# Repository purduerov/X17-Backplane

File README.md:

# Readme for X17-Backplane
This board routes signals and power between all the boards

Whenever you make a new part, download the datasheet and save it here _**and**_ with the part in the parts library

Always pull other people's changes before beginning to work
`git pull`

Be sure to push your changes after  working on them. Run:
1. `git add .` to add any files in this directory or a subdirectory
or `git add -u` to add any modified files
2. (Optional) `git clean -nX` to see what ignored files can be removed
	`git clean -fX` removes ignored files (Eagle backups)
3. `git commit -m "helpful commit message"` with a description of the work that you did
4. `git push` to push your work to github

Other helpful commands
* `git status` says information about modified and staged files
* `git log` shows the recent commits of the repository
* `git log filename.extension` show the recent commits for just that file
* `git checkout first-couple-letter-of-commit-id` lets you go back to a previous version
* `git checkout master` brings you back to the latest commit
* `git tag` lists the tags
* `git tag -a orderX -m "the version of the board placed for the X'th order"` tag a specific commit
* `git push --tags` needed to push tags to remote
* `git show orderX` show the commit log for the given tag
* `git checkout orderX` go back and interact with the files at the tagged commit

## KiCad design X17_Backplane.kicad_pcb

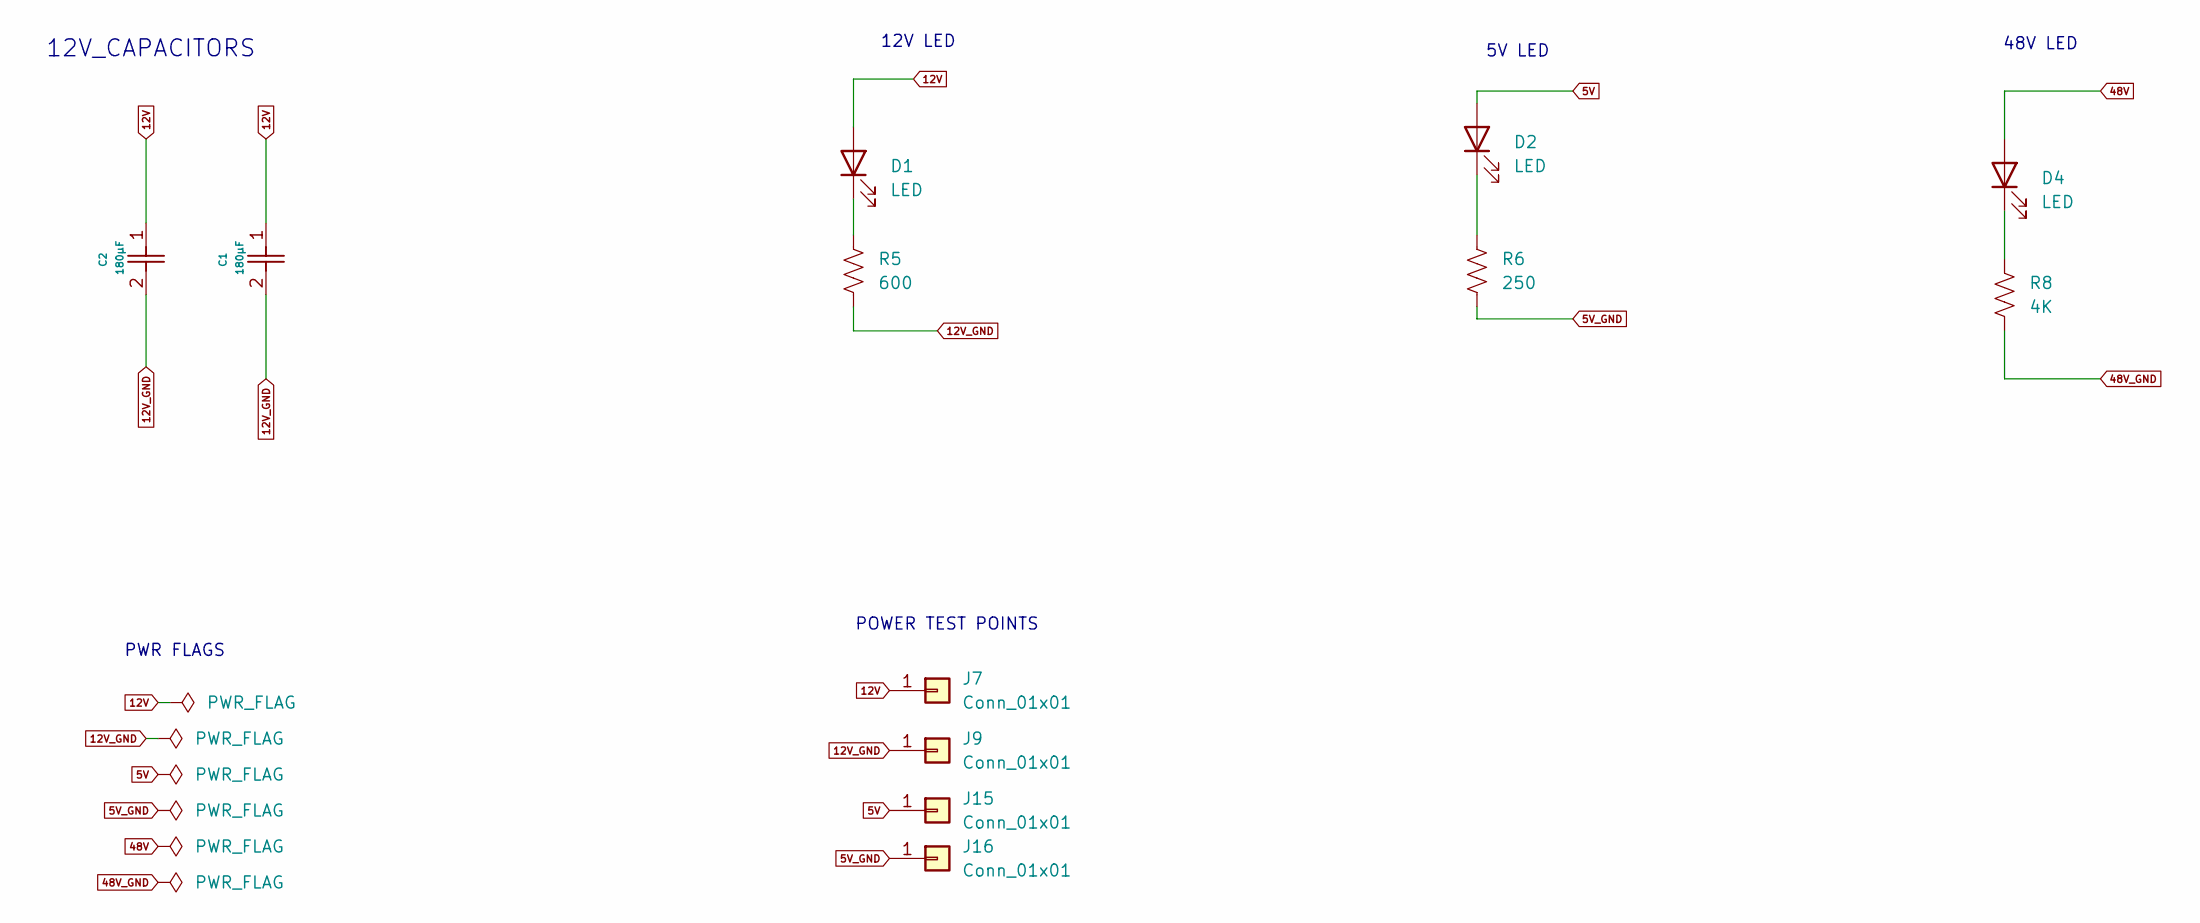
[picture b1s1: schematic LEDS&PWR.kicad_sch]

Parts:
C1, C2: 180μF; CAP_FT_F_PAN
D1, D2, D4: LED; LED_0805_2012Metric_Pad1.15x1.40mm_HandSolder
J7, J9, J15, J16: Conn_01x01; TestPoint_Pad_D4.0mm
R5: 600; R_0603_1608Metric_Pad0.98x0.95mm_HandSolder
R6: 250; R_0603_1608Metric_Pad0.98x0.95mm_HandSolder
R8: 4K; R_0603_1608Metric_Pad0.98x0.95mm_HandSolder

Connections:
5V: D2.2 (A), J15.1; also elsewhere on the board
5V_GND: J16.1, R6.2; also elsewhere on the board
12V: C1.1, C2.1, D1.2 (A), J7.1; also elsewhere on the board
12V_GND: C1.2, C2.2, J9.1, R5.2; also elsewhere on the board
48V: D4.2 (A); also elsewhere on the board
48V_GND: R8.2; also elsewhere on the board
unnamed: D1.1 (K), R5.1
unnamed: D2.1 (K), R6.1
unnamed: D4.1 (K), R8.1

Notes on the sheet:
12V_CAPACITORS
POWER TEST POINTS
12V LED
5V LED
48V LED
PWR FLAGS

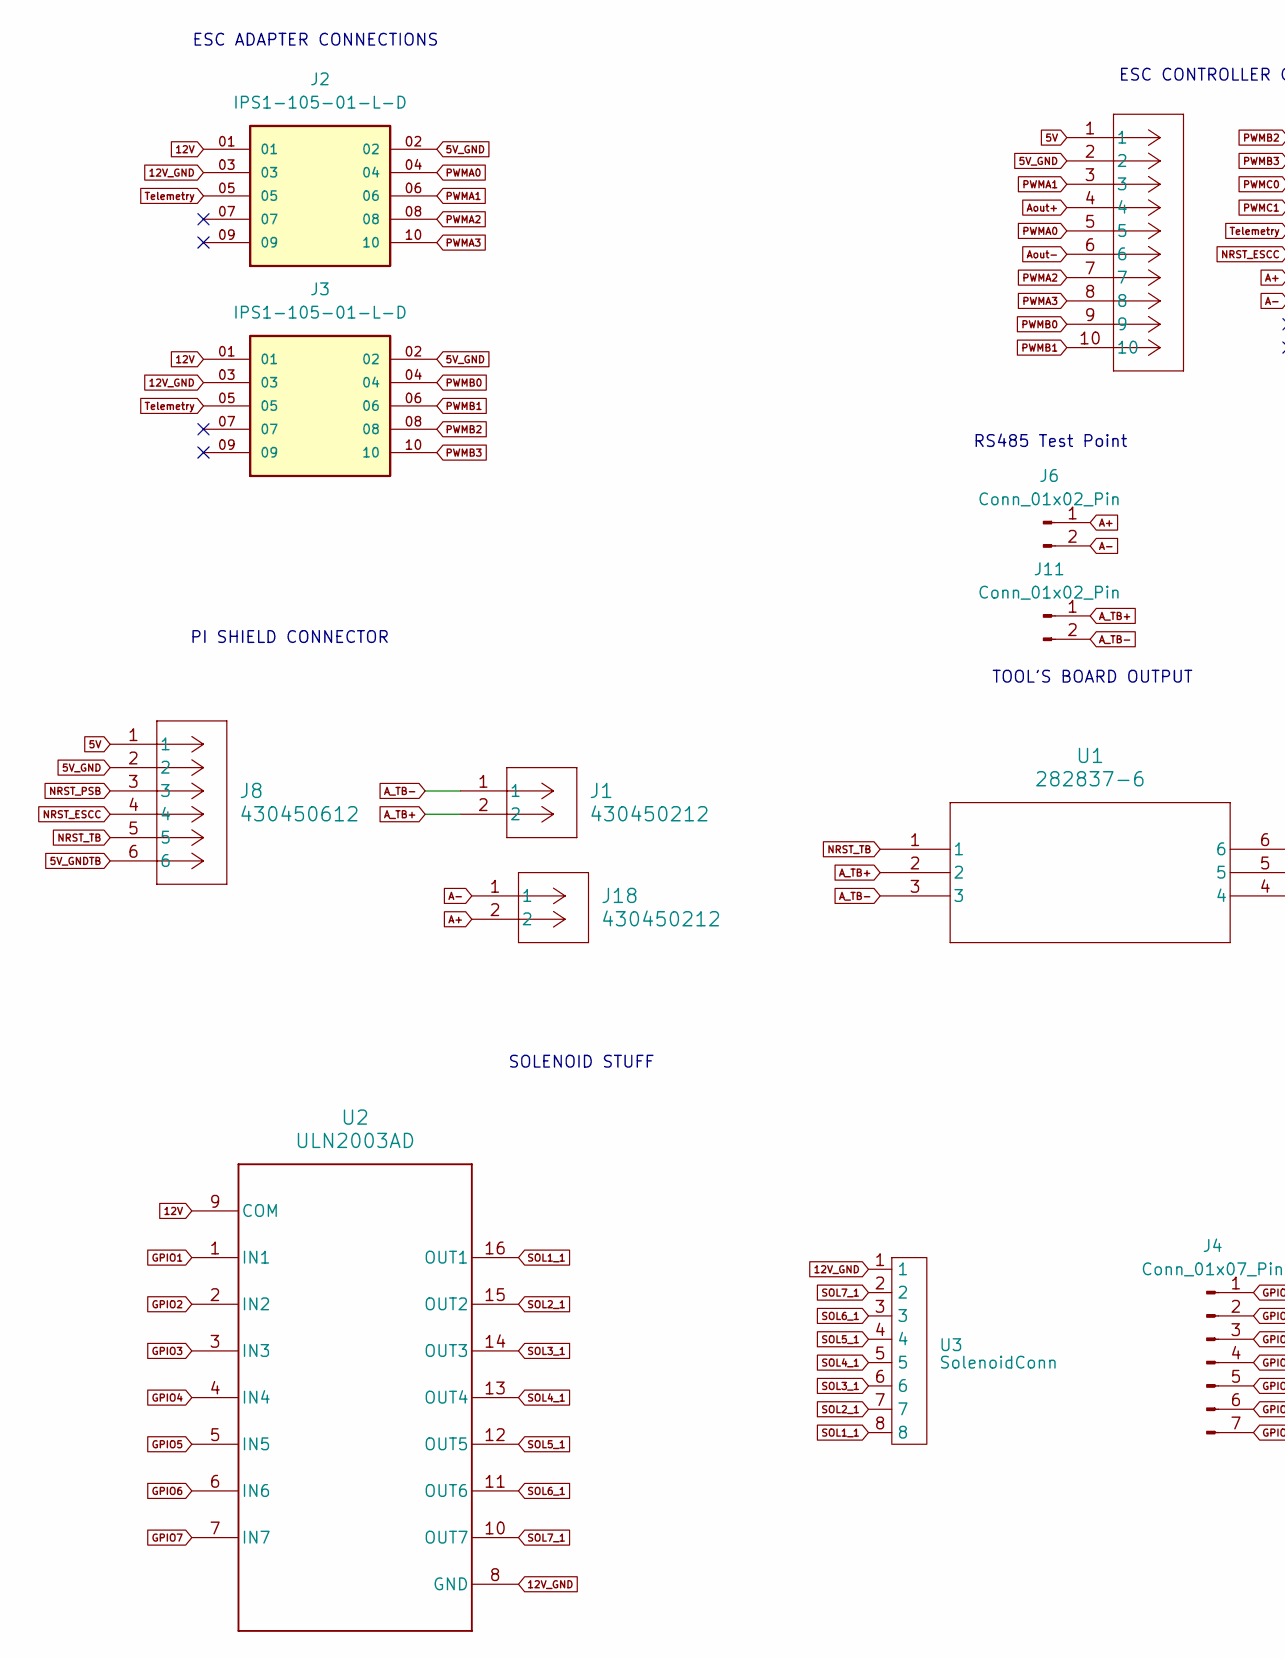
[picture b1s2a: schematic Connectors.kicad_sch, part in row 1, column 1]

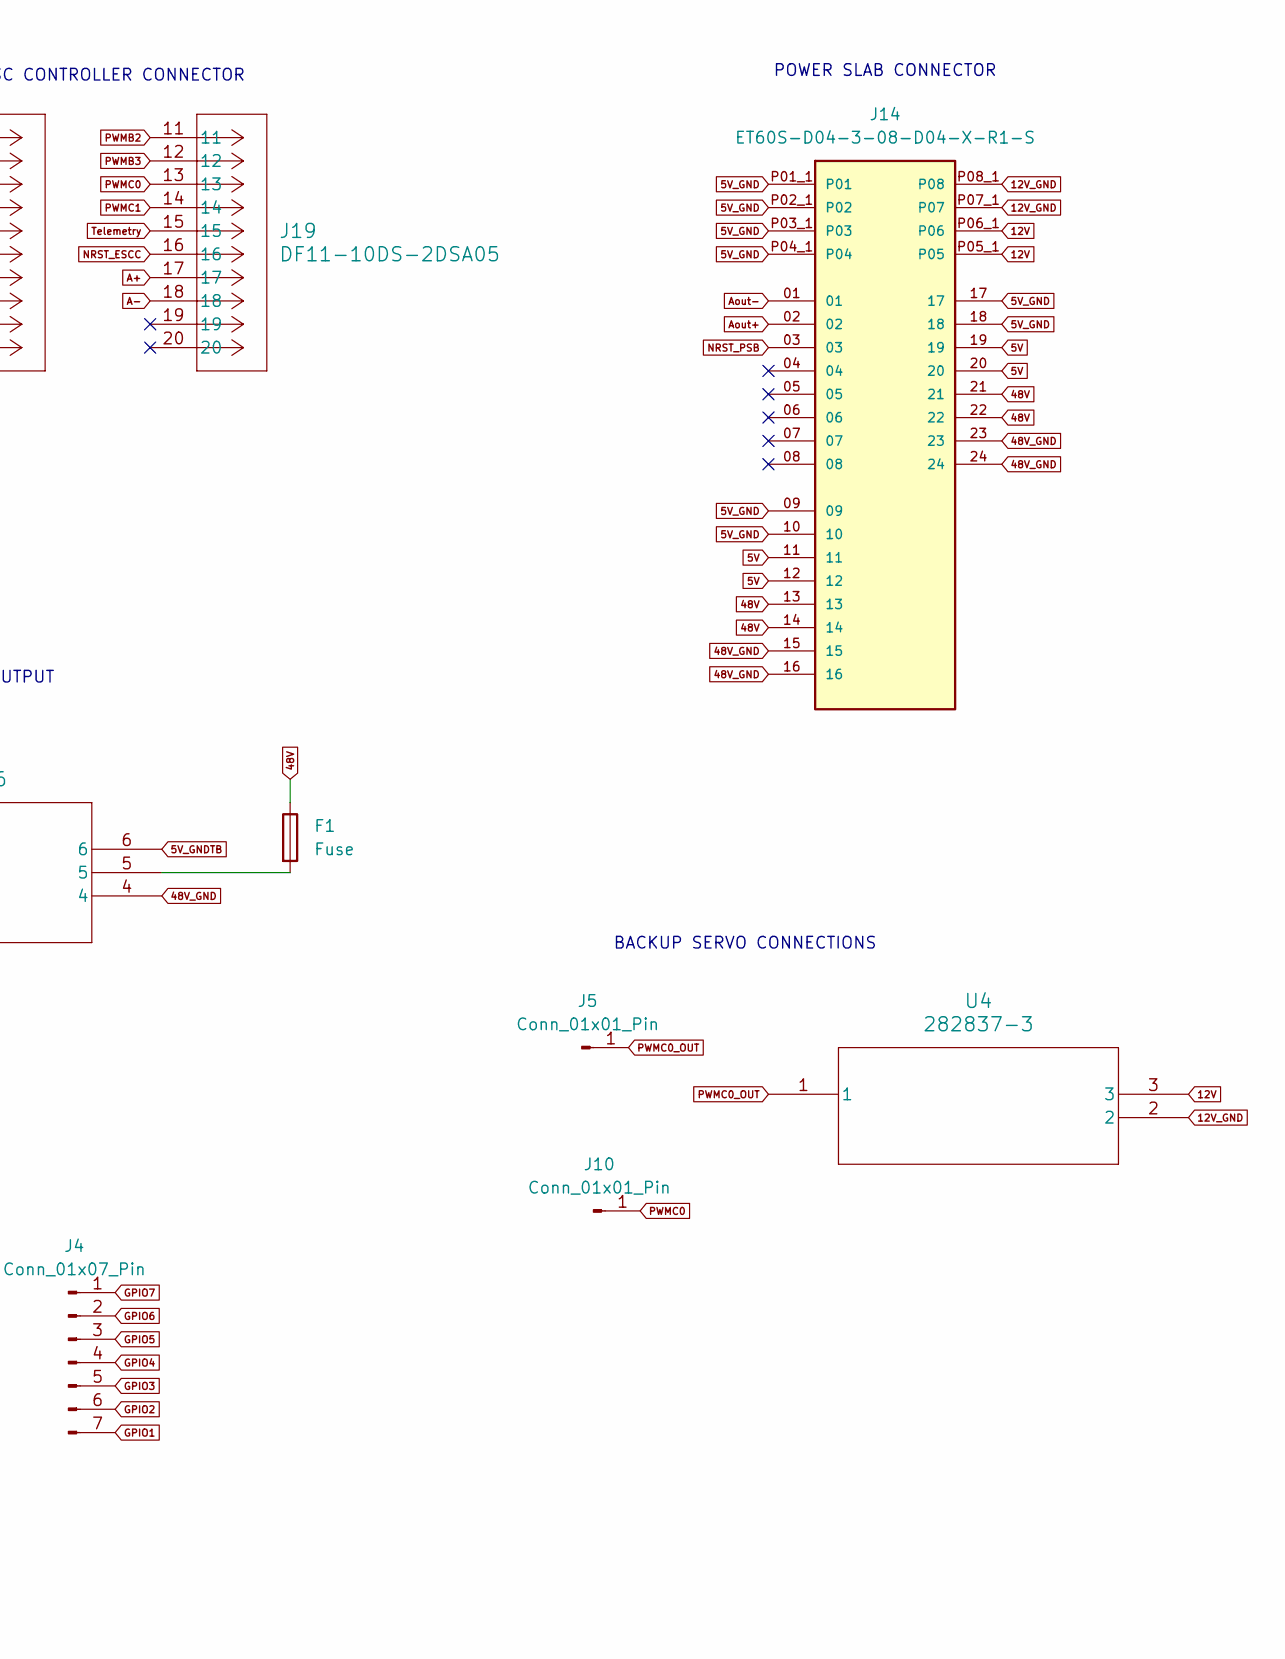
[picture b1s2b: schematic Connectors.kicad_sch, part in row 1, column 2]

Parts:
F1: Fuse; Fuse_Littelfuse-NANO2-451_453
J1, J18: 430450212; CON_430450212_MOL
J2, J3: IPS1-105-01-L-D; PWM, 12V, GND JST Connector (real); PARTREV R
J4: Conn_01x07_Pin; PinHeader_1x07_P2.54mm_Vertical
J5, J10: Conn_01x01_Pin; PinHeader_1x01_P2.54mm_Vertical
J6, J11: Conn_01x02_Pin; PinHeader_1x02_P2.54mm_Vertical
J8: 430450612; CON_430450612_MOL
J14: ET60S-D04-3-08-D04-X-R1-S; SAMTEC_ET60S-D04-3-08-D04-X-R1-S; PARTREV G
J19: DF11-10DS-2DSA05; CON10_2X5_UF_DF11_HIR
U1: 282837-6; 282837-6_TYC
U2: ULN2003AD; D0016A_L
U3: SolenoidConn; PHOENIX_1778612
U4: 282837-3; 282837-3_TYC

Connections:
5V: J8.1, J14.11, J14.12, J14.19, J14.20, J19.1; also elsewhere on the board
5V_GND: J2.02, J3.02, J8.2, J14.09, J14.10, J14.17, J14.18, J14.P01_1 (P01), J14.P02_1 (P02), J14.P03_1 (P03), J14.P04_1 (P04), J19.2; also elsewhere on the board
5V_GNDTB: J8.6, U1.6
12V: J2.01, J3.01, J14.P05_1 (P05), J14.P06_1 (P06), U2.9 (COM), U4.3; also elsewhere on the board
12V_GND: J2.03, J3.03, J14.P07_1 (P07), J14.P08_1 (P08), U2.8 (GND), U3.1, U4.2; also elsewhere on the board
48V: F1.1, J14.13, J14.14, J14.21, J14.22; also elsewhere on the board
48V_GND: J14.15, J14.16, J14.23, J14.24, U1.4; also elsewhere on the board
A+: J6.1, J18.2, J19.17
A-: J6.2, J18.1, J19.18
A_TB+: J1.2, J11.1, U1.2
A_TB-: J1.1, J11.2, U1.3
Aout+: J14.02, J19.4
Aout-: J14.01, J19.6
GPIO1: J4.7, U2.1 (IN1)
GPIO2: J4.6, U2.2 (IN2)
GPIO3: J4.5, U2.3 (IN3)
GPIO4: J4.4, U2.4 (IN4)
GPIO5: J4.3, U2.5 (IN5)
GPIO6: J4.2, U2.6 (IN6)
GPIO7: J4.1, U2.7 (IN7)
NRST_ESCC: J8.4, J19.16
NRST_PSB: J8.3, J14.03
NRST_TB: J8.5, U1.1
unnamed: F1.2, U1.5
PWMA0: J2.04, J19.5
PWMA1: J2.06, J19.3
PWMA2: J2.08, J19.7
PWMA3: J2.10, J19.8
PWMB0: J3.04, J19.9
PWMB1: J3.06, J19.10
PWMB2: J3.08, J19.11
PWMB3: J3.10, J19.12
PWMC0: J10.1, J19.13
PWMC0_OUT: J5.1, U4.1
PWMC1: J19.14
SOL1_1: U2.16 (OUT1), U3.8
SOL2_1: U2.15 (OUT2), U3.7
SOL3_1: U2.14 (OUT3), U3.6
SOL4_1: U2.13 (OUT4), U3.5
SOL5_1: U2.12 (OUT5), U3.4
SOL6_1: U2.11 (OUT6), U3.3
SOL7_1: U2.10 (OUT7), U3.2
Telemetry: J2.05, J3.05, J19.15

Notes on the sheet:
PI SHIELD CONNECTOR
TOOL'S BOARD OUTPUT
ESC CONTROLLER CONNECTOR
BACKUP SERVO CONNECTIONS
POWER SLAB CONNECTOR
ESC ADAPTER CONNECTIONS
RS485 Test Point
SOLENOID STUFF

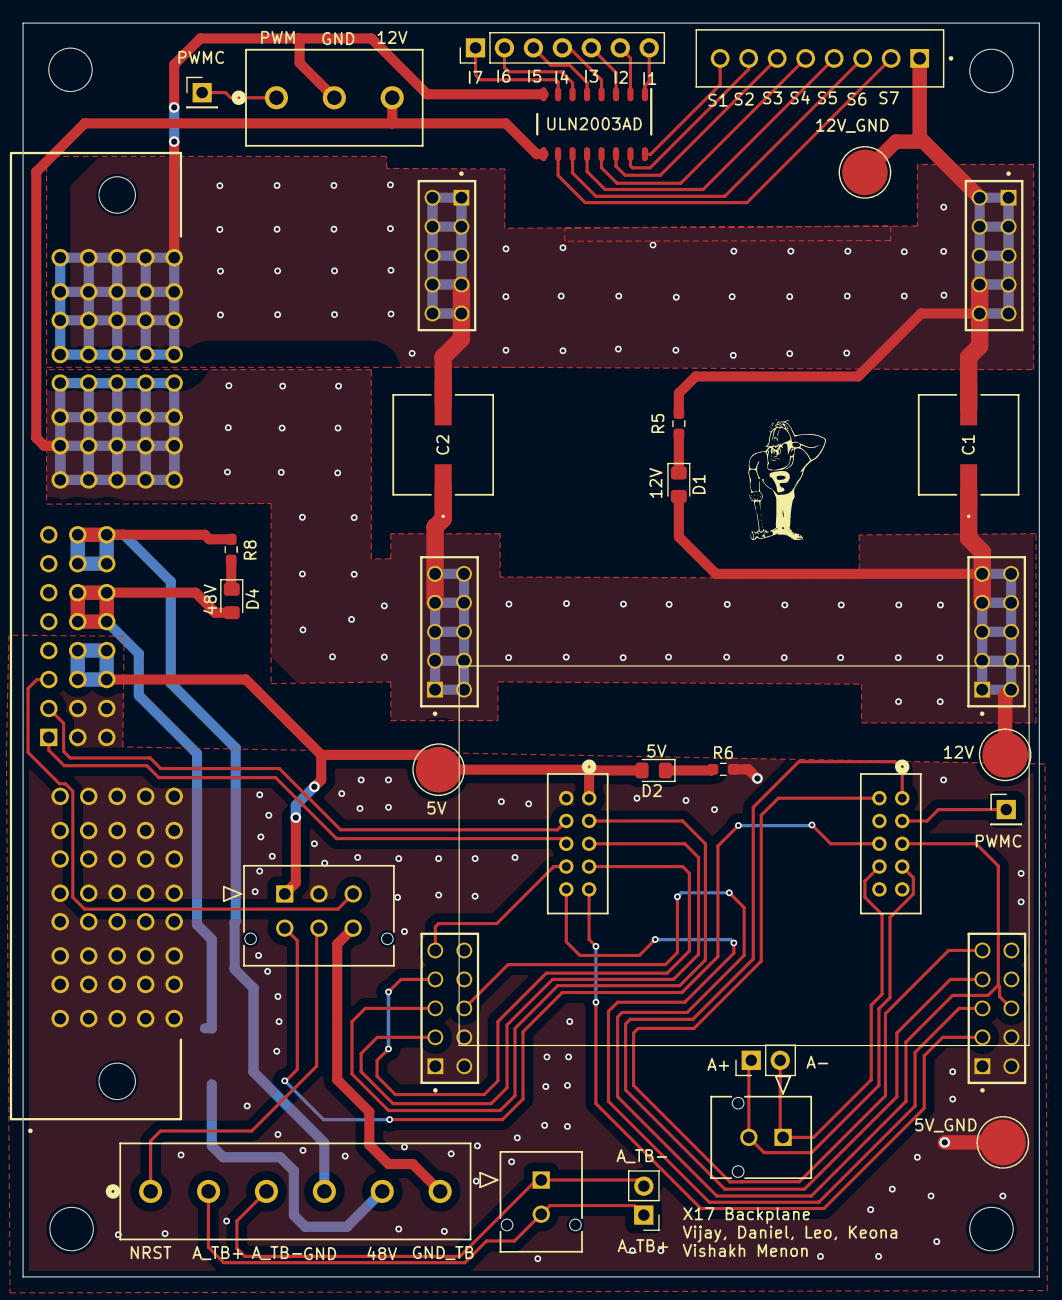
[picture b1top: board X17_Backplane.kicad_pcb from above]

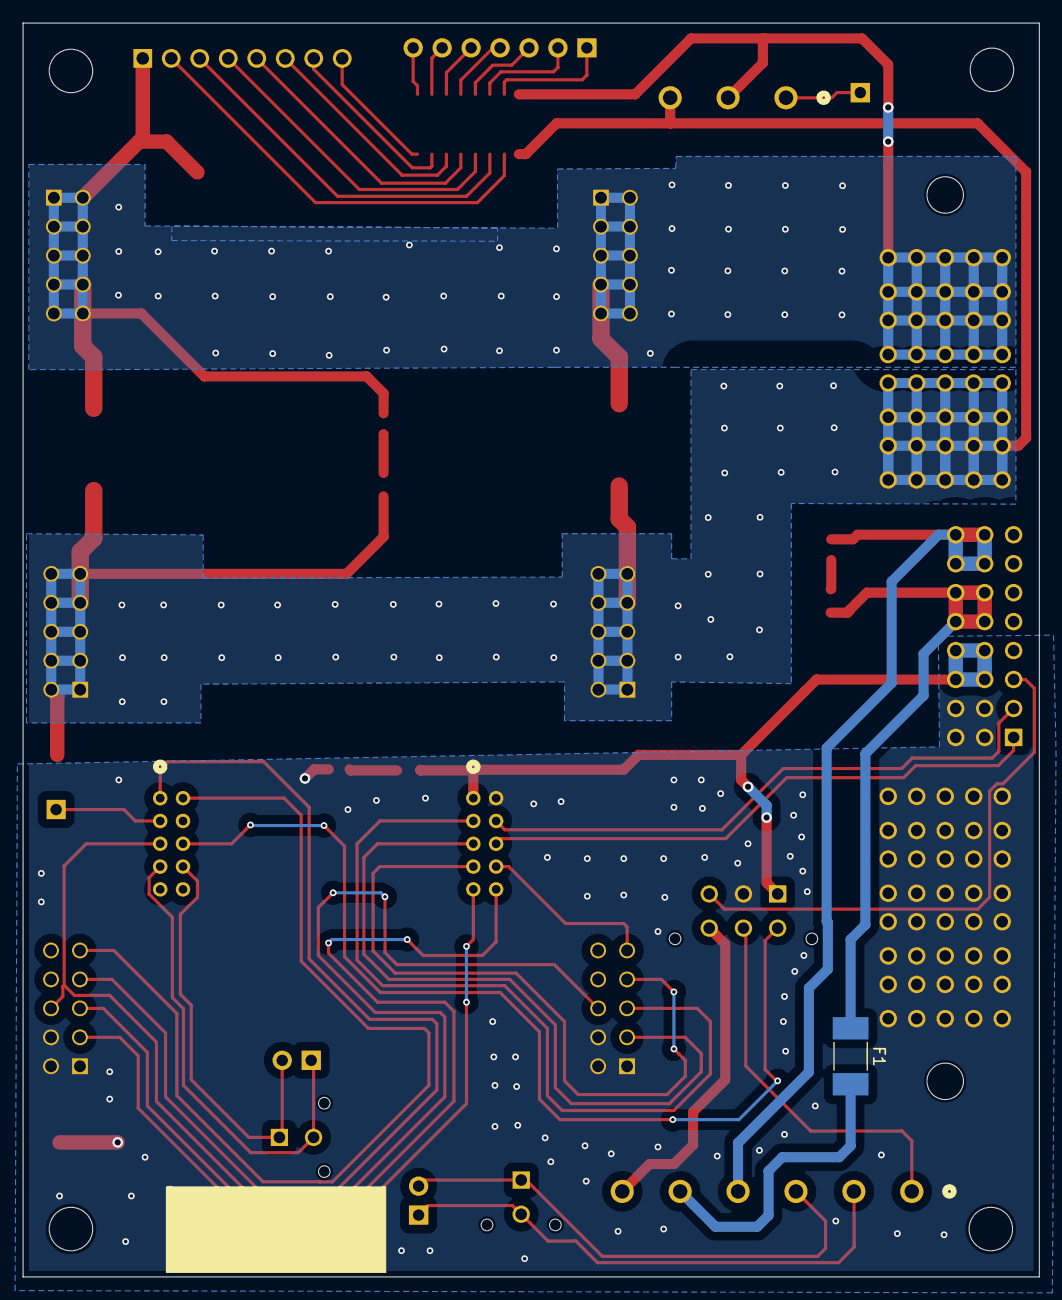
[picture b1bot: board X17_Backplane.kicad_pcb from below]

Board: 2 copper layers, 89.2 x 110.0 mm, 33 parts (5 on the bottom side), 45 nets.

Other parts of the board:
H1, H1#2, H1#3, H1#4: 6-32-HOLE

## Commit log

2024-10-09 All work thus far.
2024-10-10 Work done on 10/9/24
2024-10-12 Work on 10/12/24
2024-10-12 Final Work 10/12/2024
2024-10-17 Work done on 10/16/2024
2024-10-19 Work done on 10/19/2024
2024-10-20 Connector footprint
2024-10-20 Organized
2024-10-20 added board dimensions
2024-10-20 Work done after office hours on 10/20/24
2024-10-24 Work done on 10/23/2024
2024-10-25 Updates on 10/24/2024
2024-10-25 Update 10/25/2024 (again lol)
2024-10-31 Work done on 10/30/2024
2024-10-31 Work on 10/31/2024
2024-11-02 Work on 11/2/2024
2024-11-07 Work done on 11/06/2024
2024-11-09 Work done on 11/09/2024
2024-11-12 Work done on 11/12/2024
2024-11-13 Work done 11/13/2024
2024-11-15 Work done on 11/14/2024
2024-11-17 Work done on11/17/2024
    I'm cooked yo
2024-11-21 WORK done on 11/20/2024
    I'm losing my shiiiiiii
    #SlayedTheDayAway
2024-11-21 11/20/2024
    Yo fr tho Daniel and Vijay save my ass from these PCB demons
2024-11-21 Work done on 11/21/2024
    Made traces more size efficient(I think)
2024-11-22 Work done on 11/22/2024
2024-11-23 Work done on 11/23/2024
2024-12-14 Work done on 12/13/2024
2024-12-15 Work done on 12/14/2024
2024-12-15 More work done on 12/14/2024
2024-12-16 Work done on 12/16/2024
2024-12-16 Work done on 12/16/2024 v2
2024-12-16 Final work on 12/16
2024-12-17 Work done on 12/17/2024
2024-12-18 Work on 12/17/2024 v2
2024-12-18 work on 12/17/2024 v3
2024-12-18 Work done on 12/17/2024 final
    Am i done??????
2024-12-18 Work done on 12/18/2024
2024-12-20 Final version
2024-12-30 board review 12/30 midway
2025-01-03 changes 1/3/25
2025-01-08 correct solenoid connector + some silkscreen additions
2025-01-09 some pinout changes
2025-01-10 all ordered!
2025-01-12 update 3d model
2025-01-12 2oz has larger min spacing
